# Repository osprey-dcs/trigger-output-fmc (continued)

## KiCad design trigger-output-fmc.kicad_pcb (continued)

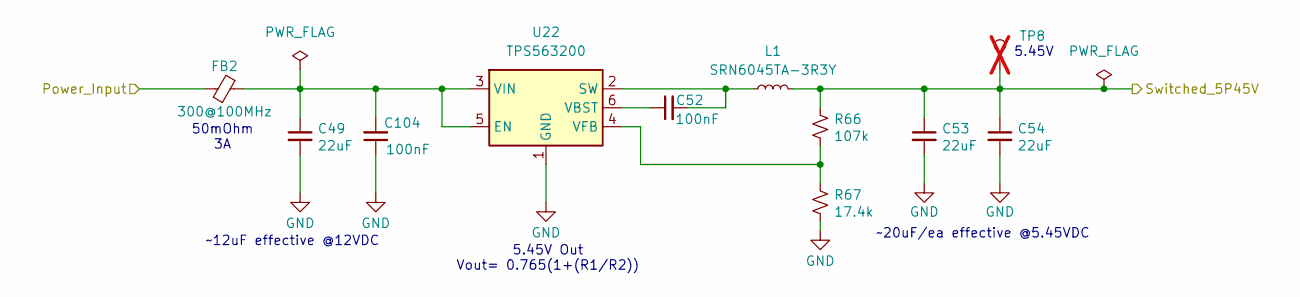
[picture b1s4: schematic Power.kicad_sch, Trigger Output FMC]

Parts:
C49, C53, C54: 22uF; C_1210_3225Metric; MPN GMK325BJ226MM-P
C52, C104: 100nF; C_0603_1608Metric; MPN GCM188R71H104KA57J
FB2: 300@100MHz; L_0805_2012Metric; MPN 742792031
L1: SRN6045TA-3R3Y; L_Bourns_SRN6045TA; MPN SRN6045TA-3R3Y
R66: 107k; R_0603_1608Metric; MPN ERJ-3EKF1073V
R67: 17.4k; R_0603_1608Metric; MPN ERJ-3EKF1742V
TP8: Keystone5000; TestPoint_Keystone_5000-5004_Miniature; MPN 5000; not fitted
U22: TPS563200; SOT-23-6; MPN TPS563200DDCT

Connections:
+12V_FMC: FB2.1; also elsewhere on the board
/Digital IO/Switched_5P45V: C53.1, C54.1, L1.2, R66.1, TP8.1; also elsewhere on the board
GND: C49.2, C53.2, C54.2, C104.1, R67.2, U22.1 (GND); also elsewhere on the board
unnamed: C49.1, C104.2, FB2.2, U22.3 (VIN), U22.5 (EN)
unnamed: C52.2, L1.1, U22.2 (SW)
unnamed: C52.1, U22.6 (VBST)
unnamed: R66.2, R67.1, U22.4 (VFB)

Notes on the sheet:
50mOhm 3A
5.45V
~20uF/ea effective @5.45VDC
5.45V Out Vout= 0.765(1+(R1/R2))
~12uF effective @12VDC

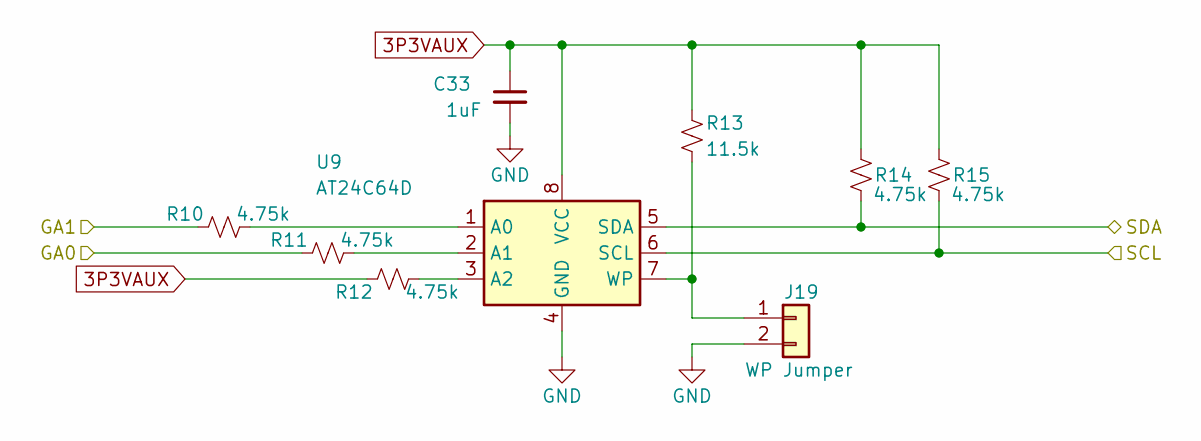
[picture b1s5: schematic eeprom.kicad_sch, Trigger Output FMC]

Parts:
C33: 1uF; C_0603_1608Metric; MPN GCM188R71E105KA64D
J19: WP Jumper; PinHeader_1x02_P2.54mm_Vertical; MPN M20-9990245
R10, R11, R12, R14, R15: 4.75k; R_0603_1608Metric; MPN RC0603FR-134K75L
R13: 11.5k; R_0603_1608Metric; MPN RC0603FR-0711K5L
U9: AT24C64D; SOIC-8_3.9x4.9mm_P1.27mm; MPN AT24C64D-SSHM-T

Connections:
3P3VAUX: C33.1, R12.1, R13.1, R14.1, R15.1, U9.8 (VCC); also elsewhere on the board
/FMC/EEPROM_GA0: R11.1; also elsewhere on the board
/FMC/EEPROM_GA1: R10.1; also elsewhere on the board
/FMC/EEPROM_SCL: R15.2, U9.6 (SCL); also elsewhere on the board
/FMC/EEPROM_SDA: R14.2, U9.5 (SDA); also elsewhere on the board
GND: C33.2, J19.2, U9.4 (GND); also elsewhere on the board
unnamed: J19.1, R13.2, U9.7 (WP)
unnamed: R10.2, U9.1 (A0)
unnamed: R11.2, U9.2 (A1)
unnamed: R12.2, U9.3 (A2)

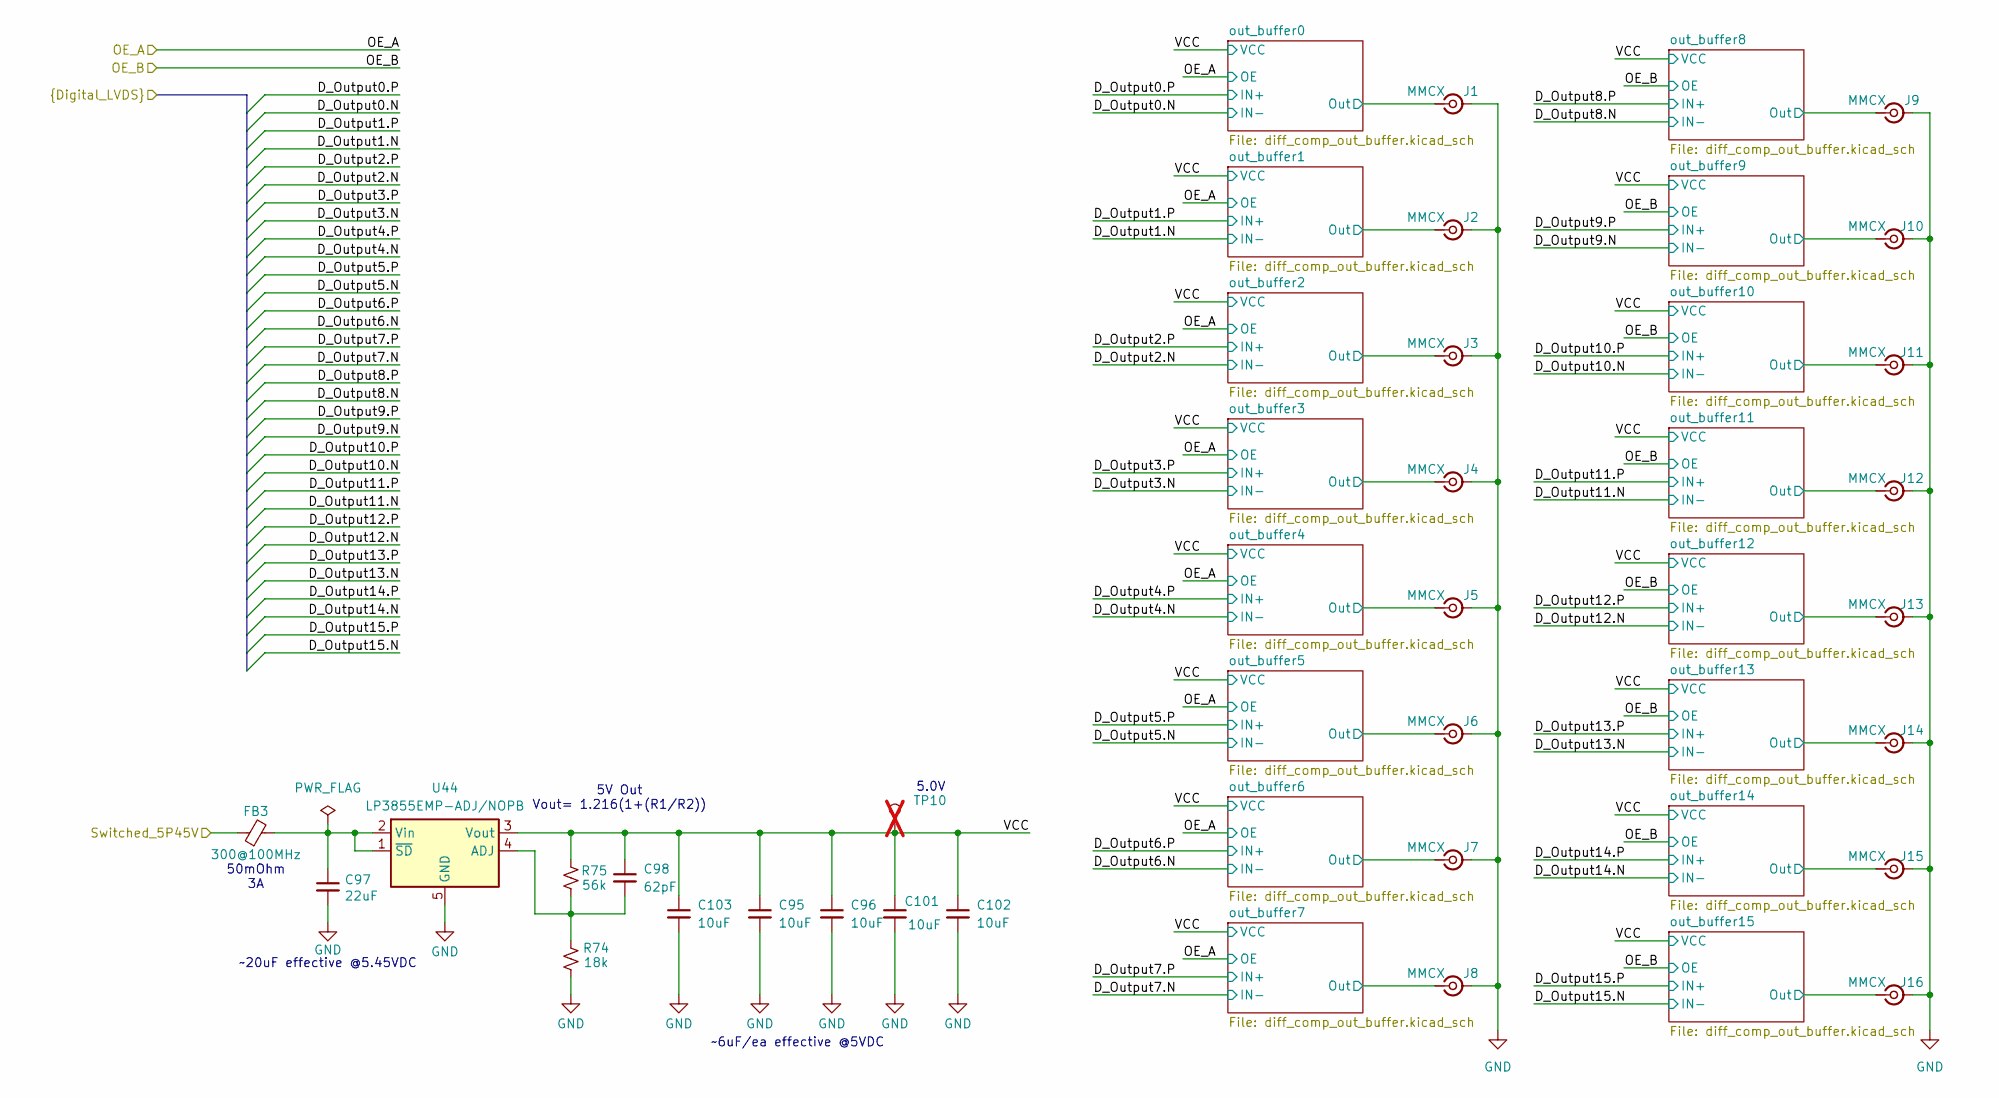
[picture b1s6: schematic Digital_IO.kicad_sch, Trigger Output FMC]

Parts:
C95, C96, C101, C102, C103: 10uF; C_0805_2012Metric; MPN TMK212BBJ106MG-T
C97: 22uF; C_1210_3225Metric; MPN GMK325BJ226MM-P
C98: 62pF; C_0603_1608Metric
FB3: 300@100MHz; L_0805_2012Metric; MPN 742792031
J1, J2, J3, J4, J5, J6, J7, J8, J9, J10, J11, J12, J13, J14, J15, J16: MMCX; MMCX_Molex_73415-1471_Vertical; MPN MMCX-J-P-H-ST-TH1
R74: 18k; R_0402_1005Metric; MPN AC0402FR-0718KL
R75: 56k; R_0402_1005Metric; MPN AF0402FR-0756KL
TP10: Keystone5000; TestPoint_Keystone_5000-5004_Miniature; MPN 5000; not fitted
U44: LP3855EMP-ADJ/NOPB; SOT-223-5; MPN LP3855EMP-ADJ/NOPB

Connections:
/Digital IO/Switched_5P45V: FB3.1; also elsewhere on the board
/Digital IO/VCC: C95.1, C96.1, C98.1, C101.1, C102.1, C103.1, R75.2, TP10.1, U44.3 (Vout); also elsewhere on the board
/Digital IO/out_buffer0/Out: J1.1 (In); also elsewhere on the board
/Digital IO/out_buffer1/Out: J2.1 (In); also elsewhere on the board
/Digital IO/out_buffer2/Out: J3.1 (In); also elsewhere on the board
/Digital IO/out_buffer3/Out: J4.1 (In); also elsewhere on the board
/Digital IO/out_buffer4/Out: J5.1 (In); also elsewhere on the board
/Digital IO/out_buffer5/Out: J6.1 (In); also elsewhere on the board
/Digital IO/out_buffer6/Out: J7.1 (In); also elsewhere on the board
/Digital IO/out_buffer7/Out: J8.1 (In); also elsewhere on the board
/Digital IO/out_buffer8/Out: J9.1 (In); also elsewhere on the board
/Digital IO/out_buffer9/Out: J10.1 (In); also elsewhere on the board
/Digital IO/out_buffer10/Out: J11.1 (In); also elsewhere on the board
/Digital IO/out_buffer11/Out: J12.1 (In); also elsewhere on the board
/Digital IO/out_buffer12/Out: J13.1 (In); also elsewhere on the board
/Digital IO/out_buffer13/Out: J14.1 (In); also elsewhere on the board
/Digital IO/out_buffer14/Out: J15.1 (In); also elsewhere on the board
/Digital IO/out_buffer15/Out: J16.1 (In); also elsewhere on the board
GND: C95.2, C96.2, C97.2, C101.2, C102.2, C103.2, J1.2 (Ext), J2.2 (Ext), J3.2 (Ext), J4.2 (Ext), J5.2 (Ext), J6.2 (Ext), J7.2 (Ext), J8.2 (Ext), J9.2 (Ext), J10.2 (Ext), J11.2 (Ext), J12.2 (Ext), J13.2 (Ext), J14.2 (Ext), J15.2 (Ext), J16.2 (Ext), R74.1, U44.5 (GND); also elsewhere on the board
unnamed: C98.2, R74.2, R75.1, U44.4 (ADJ)
unnamed: C97.1, FB3.2, U44.1 (~SD), U44.2 (Vin)

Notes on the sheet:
~20uF effective @5.45VDC
5V Out Vout= 1.216(1+(R1/R2))
50mOhm 3A
5.0V
~6uF/ea effective @5VDC

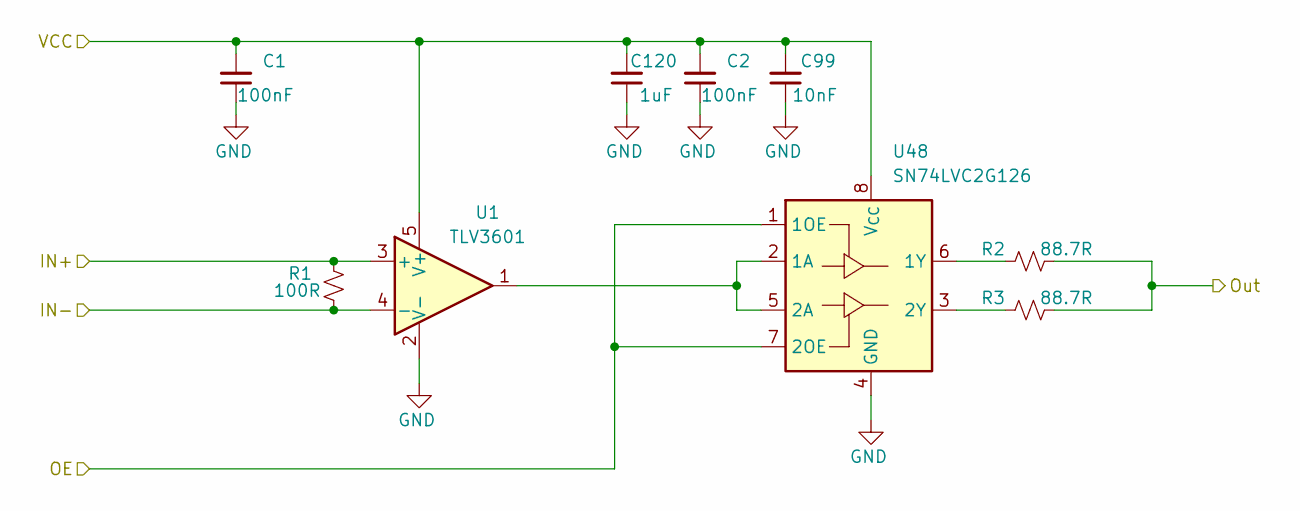
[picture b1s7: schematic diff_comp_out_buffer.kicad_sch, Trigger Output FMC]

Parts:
C1, C2: 100nF; C_0603_1608Metric; MPN GCM188R71H104KA57J
C99: 10nF; C_0603_1608Metric; MPN GRM1885C1H103JA01D
C120: 1uF; C_0603_1608Metric; MPN GCM188R71E105KA64D
R1: 100R; R_0402_1005Metric; MPN RC0402FR-07100RL
R2, R3: 88.7R; R_0805_2012Metric; MPN CRCW080588R7FKEA
U1: TLV3601; SOT-23-5; MPN TLV3601DBVR
U48: SN74LVC2G126; VSSOP-8_2.3x2mm_P0.5mm; MPN SN74LVC2G126DCUT

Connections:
/Digital IO/D_Output0.N: R1.2, U1.4 (-); also elsewhere on the board
/Digital IO/D_Output0.P: R1.1, U1.3 (+); also elsewhere on the board
/Digital IO/OE_A: U48.1 (1OE), U48.7 (2OE); also elsewhere on the board
/Digital IO/VCC: C1.2, C2.2, C99.2, C120.2, U1.5 (V+), U48.8 (V_{CC}); also elsewhere on the board
/Digital IO/out_buffer0/Out: R2.2, R3.2; also elsewhere on the board
GND: C1.1, C2.1, C99.1, C120.1, U1.2 (V-), U48.4 (GND); also elsewhere on the board
unnamed: U1.1, U48.2 (1A), U48.5 (2A)
unnamed: R2.1, U48.6 (1Y)
unnamed: R3.1, U48.3 (2Y)

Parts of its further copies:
C3, C4, C5, C6, C7, C8, C9, C10, C11, C12, C13, C14, C15, C16, C80, C81, C82, C83, C84, C85, C86, C87, C88, C89, C90, C91, C92, C93, C94, C100: 100nF; C_0603_1608Metric; MPN GCM188R71H104KA57J
C105, C106, C107, C108, C109, C110, C111, C112, C113, C114, C115, C116, C117, C118, C119: 10nF; C_0603_1608Metric; MPN GRM1885C1H103JA01D
C121, C122, C123, C124, C125, C126, C127, C128, C129, C130, C131, C132, C133, C134, C135: 1uF; C_0603_1608Metric; MPN GCM188R71E105KA64D
R4, R7, R21, R24, R27, R30, R33, R36, R39, R45, R48, R51, R54, R57, R69: 100R; R_0402_1005Metric; MPN RC0402FR-07100RL
R5, R6, R8, R9, R22, R23, R25, R26, R28, R29, R31, R32, R34, R35, R37, R38, R40, R41, R46, R47, R49, R50, R52, R53, R55, R56, R58, R59, R71, R72: 88.7R; R_0805_2012Metric; MPN CRCW080588R7FKEA
U2, U3, U6, U8, U11, U13, U15, U17, U30, U32, U34, U36, U38, U40, U42: TLV3601; SOT-23-5; MPN TLV3601DBVR
U4, U5, U7, U10, U12, U14, U16, U29, U31, U33, U35, U37, U39, U41, U43: SN74LVC2G126; VSSOP-8_2.3x2mm_P0.5mm; MPN SN74LVC2G126DCUT

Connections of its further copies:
/Digital IO/D_Output1.N: R4.2, U3.4 (-); also elsewhere on the board
/Digital IO/D_Output1.P: R4.1, U3.3 (+); also elsewhere on the board
/Digital IO/D_Output2.N: R7.2, U2.4 (-); also elsewhere on the board
/Digital IO/D_Output2.P: R7.1, U2.3 (+); also elsewhere on the board
/Digital IO/D_Output3.N: R21.2, U6.4 (-); also elsewhere on the board
/Digital IO/D_Output3.P: R21.1, U6.3 (+); also elsewhere on the board
/Digital IO/D_Output4.N: R24.2, U8.4 (-); also elsewhere on the board
/Digital IO/D_Output4.P: R24.1, U8.3 (+); also elsewhere on the board
/Digital IO/D_Output5.N: R27.2, U11.4 (-); also elsewhere on the board
/Digital IO/D_Output5.P: R27.1, U11.3 (+); also elsewhere on the board
/Digital IO/D_Output6.N: R30.2, U13.4 (-); also elsewhere on the board
/Digital IO/D_Output6.P: R30.1, U13.3 (+); also elsewhere on the board
/Digital IO/D_Output7.N: R33.2, U15.4 (-); also elsewhere on the board
/Digital IO/D_Output7.P: R33.1, U15.3 (+); also elsewhere on the board
/Digital IO/D_Output8.N: R36.2, U17.4 (-); also elsewhere on the board
/Digital IO/D_Output8.P: R36.1, U17.3 (+); also elsewhere on the board
/Digital IO/D_Output9.N: R39.2, U30.4 (-); also elsewhere on the board
/Digital IO/D_Output9.P: R39.1, U30.3 (+); also elsewhere on the board
/Digital IO/D_Output10.N: R45.2, U32.4 (-); also elsewhere on the board
/Digital IO/D_Output10.P: R45.1, U32.3 (+); also elsewhere on the board
/Digital IO/D_Output11.N: R48.2, U34.4 (-); also elsewhere on the board
/Digital IO/D_Output11.P: R48.1, U34.3 (+); also elsewhere on the board
/Digital IO/D_Output12.N: R51.2, U36.4 (-); also elsewhere on the board
/Digital IO/D_Output12.P: R51.1, U36.3 (+); also elsewhere on the board
/Digital IO/D_Output13.N: R54.2, U38.4 (-); also elsewhere on the board
/Digital IO/D_Output13.P: R54.1, U38.3 (+); also elsewhere on the board
/Digital IO/D_Output14.N: R57.2, U40.4 (-); also elsewhere on the board
/Digital IO/D_Output14.P: R57.1, U40.3 (+); also elsewhere on the board
/Digital IO/D_Output15.N: R69.2, U42.4 (-); also elsewhere on the board
/Digital IO/D_Output15.P: R69.1, U42.3 (+); also elsewhere on the board
/Digital IO/OE_A: U4.1 (1OE), U4.7 (2OE), U5.1 (1OE), U5.7 (2OE), U7.1 (1OE), U7.7 (2OE), U10.1 (1OE), U10.7 (2OE), U12.1 (1OE), U12.7 (2OE), U14.1 (1OE), U14.7 (2OE), U16.1 (1OE), U16.7 (2OE); also elsewhere on the board
/Digital IO/OE_B: U29.1 (1OE), U29.7 (2OE), U31.1 (1OE), U31.7 (2OE), U33.1 (1OE), U33.7 (2OE), U35.1 (1OE), U35.7 (2OE), U37.1 (1OE), U37.7 (2OE), U39.1 (1OE), U39.7 (2OE), U41.1 (1OE), U41.7 (2OE), U43.1 (1OE), U43.7 (2OE); also elsewhere on the board
/Digital IO/VCC: C3.2, C4.2, C5.2, C6.2, C7.2, C8.2, C9.2, C10.2, C11.2, C12.2, C13.2, C14.2, C15.2, C16.2, C80.2, C81.2, C82.2, C83.2, C84.2, C85.2, C86.2, C87.2, C88.2, C89.2, C90.2, C91.2, C92.2, C93.2, C94.2, C100.2, C105.2, C106.2, C107.2, C108.2, C109.2, C110.2, C111.2, C112.2, C113.2, C114.2, C115.2, C116.2, C117.2, C118.2, C119.2, C121.2, C122.2, C123.2, C124.2, C125.2, C126.2, C127.2, C128.2, C129.2, C130.2, C131.2, C132.2, C133.2, C134.2, C135.2, U2.5 (V+), U3.5 (V+), U4.8 (V_{CC}), U5.8 (V_{CC}), U6.5 (V+), U7.8 (V_{CC}), U8.5 (V+), U10.8 (V_{CC}), U11.5 (V+), U12.8 (V_{CC}), U13.5 (V+), U14.8 (V_{CC}), U15.5 (V+), U16.8 (V_{CC}), U17.5 (V+), U29.8 (V_{CC}), U30.5 (V+), U31.8 (V_{CC}), U32.5 (V+), U33.8 (V_{CC}), U34.5 (V+), U35.8 (V_{CC}), U36.5 (V+), U37.8 (V_{CC}), U38.5 (V+), U39.8 (V_{CC}), U40.5 (V+), U41.8 (V_{CC}), U42.5 (V+), U43.8 (V_{CC}); also elsewhere on the board
/Digital IO/out_buffer1/Out: R5.2, R6.2; also elsewhere on the board
/Digital IO/out_buffer2/Out: R8.2, R9.2; also elsewhere on the board
/Digital IO/out_buffer3/Out: R22.2, R23.2; also elsewhere on the board
/Digital IO/out_buffer4/Out: R25.2, R26.2; also elsewhere on the board
/Digital IO/out_buffer5/Out: R28.2, R29.2; also elsewhere on the board
/Digital IO/out_buffer6/Out: R31.2, R32.2; also elsewhere on the board
/Digital IO/out_buffer7/Out: R34.2, R35.2; also elsewhere on the board
/Digital IO/out_buffer8/Out: R37.2, R38.2; also elsewhere on the board
/Digital IO/out_buffer9/Out: R40.2, R41.2; also elsewhere on the board
/Digital IO/out_buffer10/Out: R46.2, R47.2; also elsewhere on the board
/Digital IO/out_buffer11/Out: R49.2, R50.2; also elsewhere on the board
/Digital IO/out_buffer12/Out: R52.2, R53.2; also elsewhere on the board
/Digital IO/out_buffer13/Out: R55.2, R56.2; also elsewhere on the board
/Digital IO/out_buffer14/Out: R58.2, R59.2; also elsewhere on the board
/Digital IO/out_buffer15/Out: R71.2, R72.2; also elsewhere on the board
GND: C3.1, C4.1, C5.1, C6.1, C7.1, C8.1, C9.1, C10.1, C11.1, C12.1, C13.1, C14.1, C15.1, C16.1, C80.1, C81.1, C82.1, C83.1, C84.1, C85.1, C86.1, C87.1, C88.1, C89.1, C90.1, C91.1, C92.1, C93.1, C94.1, C100.1, C105.1, C106.1, C107.1, C108.1, C109.1, C110.1, C111.1, C112.1, C113.1, C114.1, C115.1, C116.1, C117.1, C118.1, C119.1, C121.1, C122.1, C123.1, C124.1, C125.1, C126.1, C127.1, C128.1, C129.1, C130.1, C131.1, C132.1, C133.1, C134.1, C135.1, U2.2 (V-), U3.2 (V-), U4.4 (GND), U5.4 (GND), U6.2 (V-), U7.4 (GND), U8.2 (V-), U10.4 (GND), U11.2 (V-), U12.4 (GND), U13.2 (V-), U14.4 (GND), U15.2 (V-), U16.4 (GND), U17.2 (V-), U29.4 (GND), U30.2 (V-), U31.4 (GND), U32.2 (V-), U33.4 (GND), U34.2 (V-), U35.4 (GND), U36.2 (V-), U37.4 (GND), U38.2 (V-), U39.4 (GND), U40.2 (V-), U41.4 (GND), U42.2 (V-), U43.4 (GND); also elsewhere on the board
unnamed: U3.1, U4.2 (1A), U4.5 (2A)
unnamed: R5.1, U4.6 (1Y)
unnamed: R6.1, U4.3 (2Y)
unnamed: U2.1, U5.2 (1A), U5.5 (2A)
unnamed: R8.1, U5.6 (1Y)
unnamed: R9.1, U5.3 (2Y)
unnamed: U6.1, U7.2 (1A), U7.5 (2A)
unnamed: R22.1, U7.6 (1Y)
unnamed: R23.1, U7.3 (2Y)
unnamed: U8.1, U10.2 (1A), U10.5 (2A)
unnamed: R25.1, U10.6 (1Y)
unnamed: R26.1, U10.3 (2Y)
unnamed: U11.1, U12.2 (1A), U12.5 (2A)
unnamed: R28.1, U12.6 (1Y)
unnamed: R29.1, U12.3 (2Y)
unnamed: U13.1, U14.2 (1A), U14.5 (2A)
unnamed: R31.1, U14.6 (1Y)
unnamed: R32.1, U14.3 (2Y)
unnamed: U15.1, U16.2 (1A), U16.5 (2A)
unnamed: R34.1, U16.6 (1Y)
unnamed: R35.1, U16.3 (2Y)
unnamed: U17.1, U29.2 (1A), U29.5 (2A)
unnamed: R37.1, U29.6 (1Y)
unnamed: R38.1, U29.3 (2Y)
unnamed: U30.1, U31.2 (1A), U31.5 (2A)
unnamed: R40.1, U31.6 (1Y)
unnamed: R41.1, U31.3 (2Y)
unnamed: U32.1, U33.2 (1A), U33.5 (2A)
unnamed: R46.1, U33.6 (1Y)
unnamed: R47.1, U33.3 (2Y)
unnamed: U34.1, U35.2 (1A), U35.5 (2A)
unnamed: R49.1, U35.6 (1Y)
unnamed: R50.1, U35.3 (2Y)
unnamed: U36.1, U37.2 (1A), U37.5 (2A)
unnamed: R52.1, U37.6 (1Y)
unnamed: R53.1, U37.3 (2Y)
unnamed: U38.1, U39.2 (1A), U39.5 (2A)
unnamed: R55.1, U39.6 (1Y)
unnamed: R56.1, U39.3 (2Y)
unnamed: U40.1, U41.2 (1A), U41.5 (2A)
unnamed: R58.1, U41.6 (1Y)
unnamed: R59.1, U41.3 (2Y)
unnamed: U42.1, U43.2 (1A), U43.5 (2A)
unnamed: R71.1, U43.6 (1Y)
unnamed: R72.1, U43.3 (2Y)

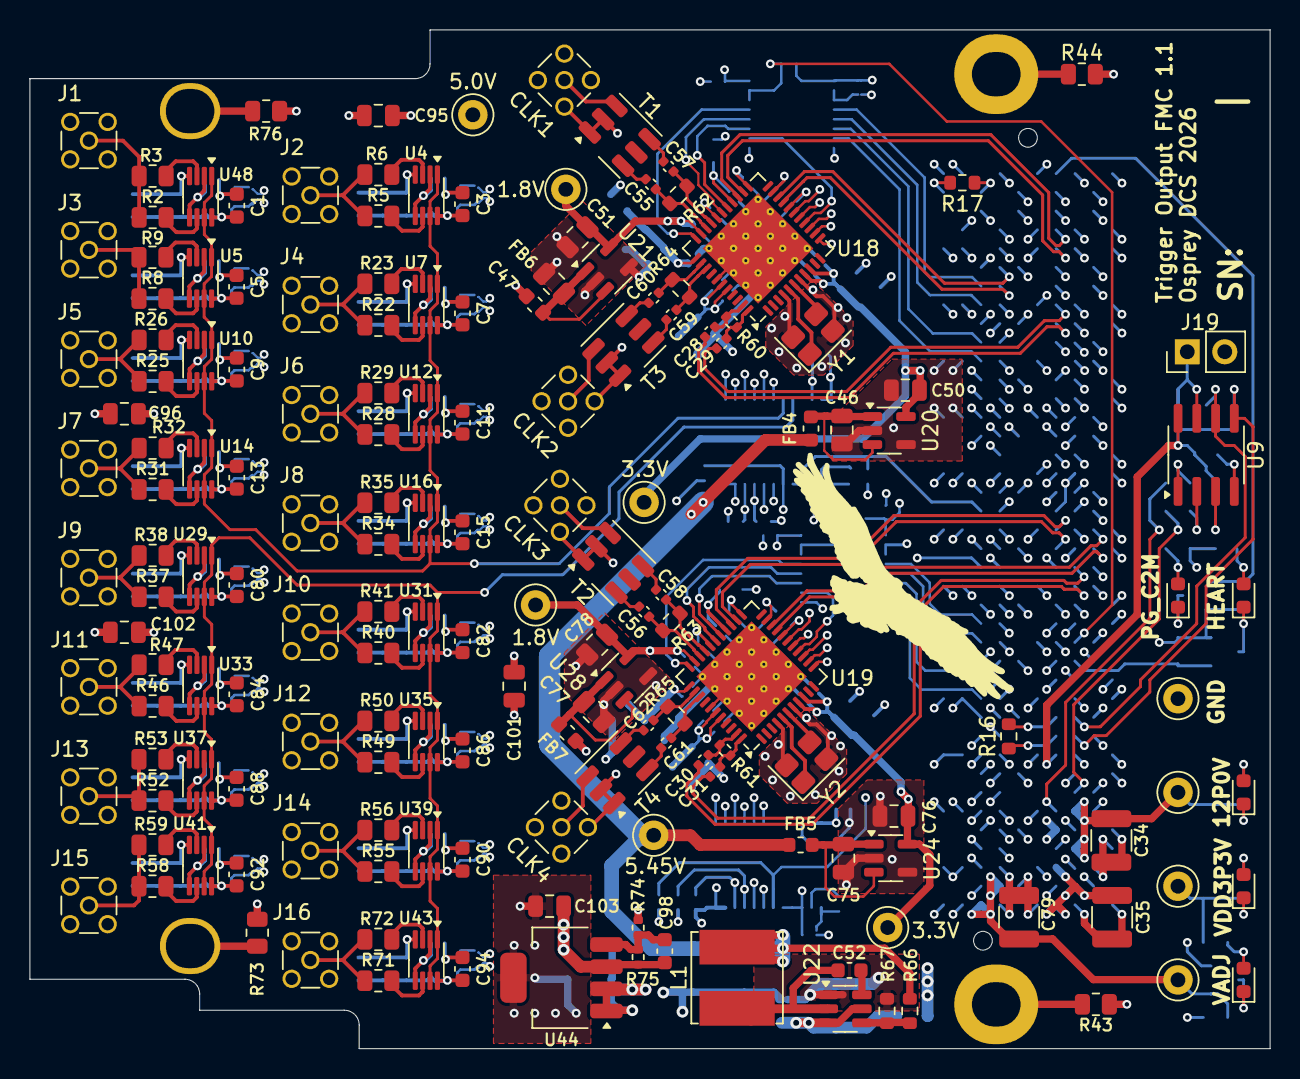
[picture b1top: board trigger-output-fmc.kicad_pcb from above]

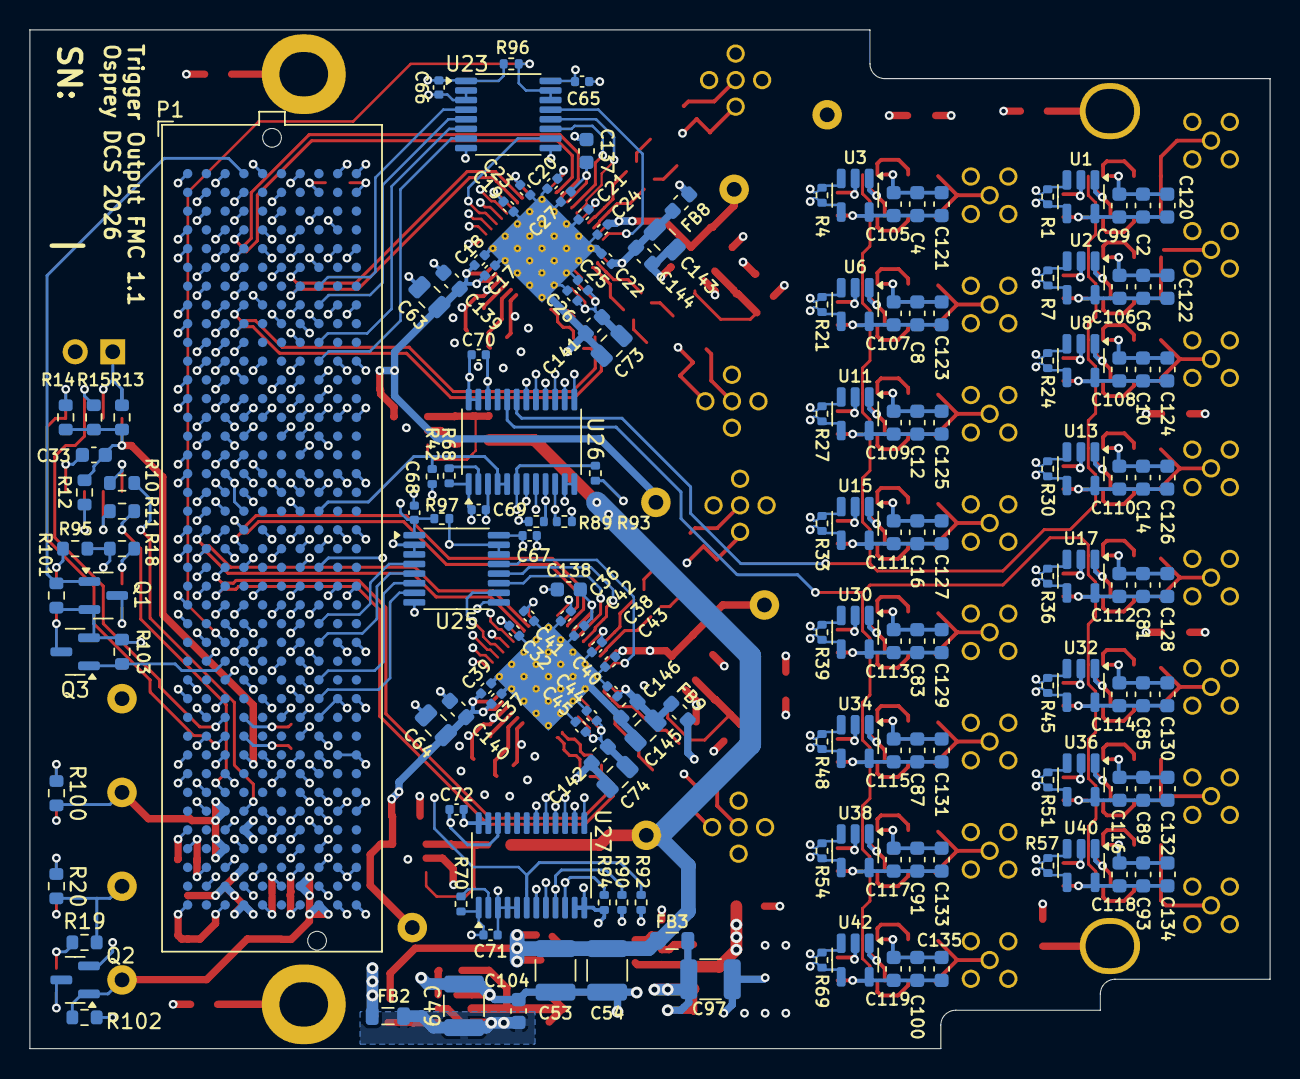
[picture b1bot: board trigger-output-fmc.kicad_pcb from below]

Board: 8 copper layers, 84.0 x 69.0 mm, 338 parts (167 on the bottom side), 229 nets.

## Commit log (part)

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2026-03-14 Start of project
    - Based on FMC Template
    - Layout needs to be finished
    - Some Schematic cleanup is needed
    - All BOM/manufacture data needs to be looked over
2026-03-17 Completed Schematic
    Completed Schematic Draft
    - Includes careful pin mapping to avoid conflicts with other firmwares
    - Roughed out LCB layout high speed traces, and FMC breakouts.
    Layout and BOM are still WIP
2026-03-26 Updated Schematic and continued layout work
    schematic:
    - Added 0ohm resistor in power section
    - Added pull up and down to digital lines to define powerup behavior
    - Added some power filter between jitter cleaner IC's
    layout:
    -Overall Still WIP
2026-04-02 Revised Si5394 part and schematic changes
    - Revised Si5394 part
    - Changed OE pin connection on Si5394
    - Removed OE from SPI group
2026-04-07 Updated Cleaner Control Signaling
2026-04-09 Schematic Updates
    -Added Heartbeat LED
    -Assigned Jitter cleaner OE to FPGA pins
    -Changed LDO parts
2026-04-16 Finalized Schematic and Updated Layout
2026-04-28 Updated Layout
    - parts floor planed
    - need to finish digital IO routing
2026-04-30 Layout draft nearly complete
    - Changed some digital IO pinout on the FMC
    - Most areas routed
2026-05-05 Draft Layout Complete
    -Draft Layout Complete
    - Silkscreen need to be complete
    - some Digital IO swapped FMC pins
2026-05-07 Final Draft - Ready to Review
    Things to do:
    Round diff traces before generting fabrication files
    Change name of project to 'trigger output fmc'
    Align this with recent updates to fmc-template
    Updates:
    - Cleaned up BOM
2026-05-07 Final Draft - Ready for review
    Updates:
    - Changed area behind FMC connector to match the new Osprey FMC template
    - This includes a new 12V LED, more robust power input traces, arranged elements for readability.
    Things to do:
    Round diff traces before generating fabrication files
    Change name of project to 'trigger output fmc'
2026-06-23 Changed Trigger Outputs Topology
    - Changed to a comp to digital TX design
    - Added power section to support this change
2026-06-24 Updated Layout - roughly floor planed all parts on board
    - All parts fit on the board but routing may still result in power sections moving
2026-06-30 Added Level Shifter schematic & moved symbols
    - Created a separate Level Shifter schematic to prepare use of some gates for Digital output enables.
2026-06-30 Added Draft Design Document
    - Added Draft Design Document * still needs polish *
2026-06-30 fix case of Level_Shifter sheet name
2026-06-30 GHA add kibot
2026-06-30 DRC disabled while artwork unfinished
